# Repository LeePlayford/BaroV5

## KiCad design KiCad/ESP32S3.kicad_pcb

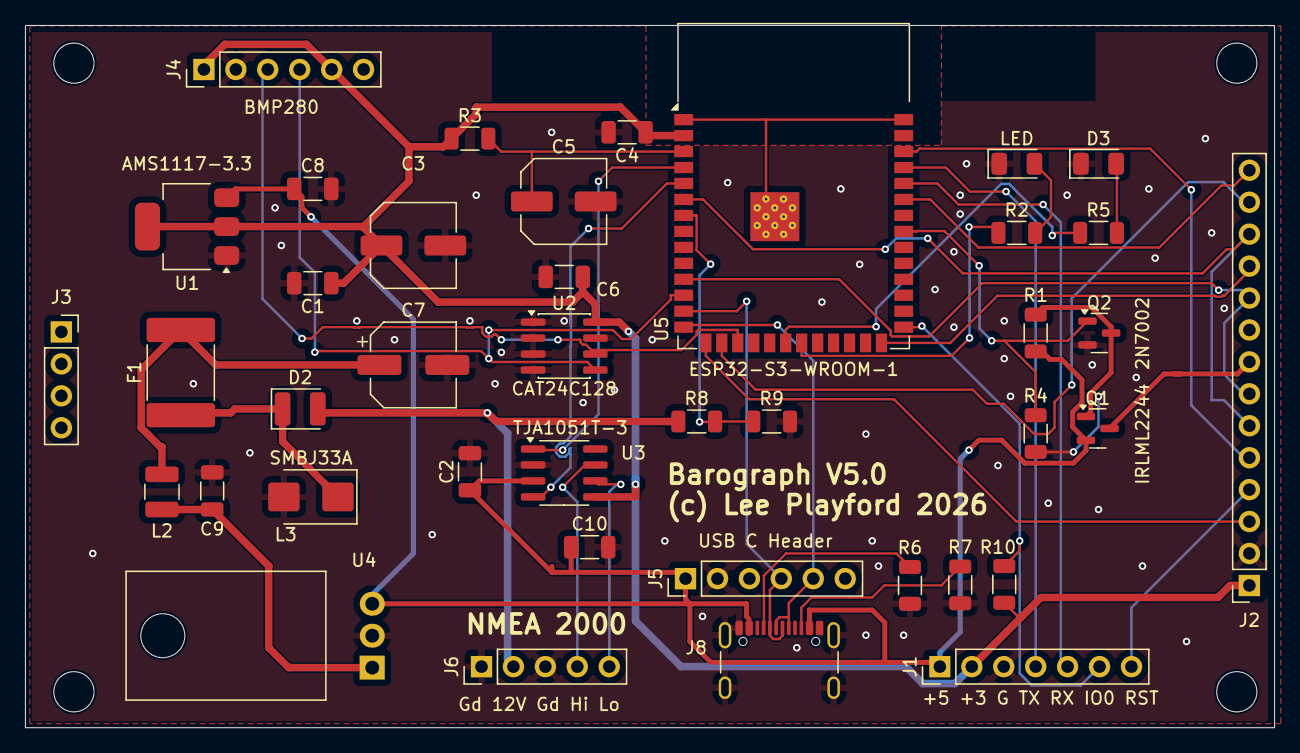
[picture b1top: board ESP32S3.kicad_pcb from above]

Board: 2 copper layers, 99.4 x 55.9 mm, 44 parts (0 on the bottom side), 38 nets.

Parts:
C1, C2, C4, C6, C8, C9, C10: 100nF; C_1206_3216Metric
C3: 22uF; C_Elec_6.3x5.4
C5: 10uF; C_Elec_6.3x5.4
C7: 100uf; CP_Elec_6.3x5.8
D1, D3: LED; LED_1206_3216Metric
D2: D; D_1210_3225Metric
F1: 2920L110/60MR; Fuse_2920_7451Metric
H1, H2, H3, H4: MountingHole; MountingHole_3.2mm_M3
J1: +5 +3 G TX RX IO0 RST; PinHeader_1x07_P2.54mm_Vertical
J2: Conn_01x14_Socket; PinSocket_1x14_P2.54mm_Vertical
J3: Conn_01x04_Socket; PinSocket_1x04_P2.54mm_Vertical
J4: BMP280; PinHeader_1x06_P2.54mm_Vertical
J5: USB C Header; PinHeader_1x06_P2.54mm_Vertical
J6: Gd 12V Gd Hi Lo; PinHeader_1x05_P2.54mm_Vertical
J8: USB_C_Receptacle_USB2.0_16P; USB_C_Receptacle_GCT_USB4105-xx-A_16P_TopMnt_Horizontal
L2: 33uH; L_1210_3225Metric
L3: SMBJ33A; D_SMB
Q1: IRLML2244; SOT-23
Q2: 2N7002; SOT-23
R1: 1k; R_1206_3216Metric
R2, R5: 120R; R_1206_3216Metric
R3, R4, R9, R10: 10K; R_1206_3216Metric
R6, R7: 5k1; R_1206_3216Metric
R8: 50k; R_1206_3216Metric
U1: AMS1117-3.3; SOT-223-3_TabPin2
U2: CAT24C128; SOIC-8_3.9x4.9mm_P1.27mm
U3: TJA1051T-3; SOIC-8_3.9x4.9mm_P1.27mm
U4: LM7805_TO220; TO-220-3_Horizontal_TabDown
U5: ESP32-S3-WROOM-1

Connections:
+3V3: C1.1, C3.1, C4.1, C6.1, J1.2, J2.1, J4.1, J4.5, R3.1, R10.1, U1.2 (VO), U2.8 (VCC), U3.5 (VIO), U5.2 (3V3)
+5V: C2.1, C8.1, C10.1, J1.1, J5.1, J8.A4 (VBUS), J8.A9 (VBUS), J8.B4 (VBUS), J8.B9 (VBUS), Q1.2 (S), R1.2, U1.3 (VI), U3.3 (VCC), U4.3 (VO)
+12V: D2.2 (A), J6.2, R8.1
BACKLIGHT: J2.8, Q1.3 (D)
BL_GPIO: Q2.1 (G), R4.1, U5.33 (IO40)
CAN_H: J6.4, U3.7 (CANH)
CAN_L: J6.5, U3.6 (CANL)
CAN_RX: U3.4 (RXD), U5.5 (IO5)
CAN_TX: U3.1 (TXD), U5.4 (IO4)
EN_RESET: J1.7, J2.4
GND: C1.2, C2.2, C3.2, C4.2, C5.2, C6.2, C7.2, C8.2, C9.2, C10.2, D1.1 (K), D3.1 (K), J1.3, J2.2, J4.2, J5.2, J6.1, J6.3, J8.A1 (GND), J8.A12 (GND), J8.B1 (GND), J8.B12 (GND), J8.S1 (SHIELD), L3.2, Q2.2 (S), R4.2, R6.2, R7.2, R9.2, U1.1 (GND), U2.1 (A0), U2.2 (A1), U2.3 (A2), U2.4 (GND), U2.7 (WP), U3.2 (GND), U4.2 (GND)
IO0: J1.6, R10.2, U5.27 (IO0)
LCD_CLK: J2.7, J2.10, U5.11 (IO18)
LCD_CS: J2.3, U5.15 (IO3)
LCD_MOSI: J2.6, J2.12, U5.6 (IO6)
LCD_RS: J2.5, U5.38 (IO2)
LED_01: R5.1, U5.20 (IO12)
LED_02: R2.1, U5.21 (IO13)
unnamed: C7.1, F1.2, L2.1
unnamed: D1.2 (A), R2.2
unnamed: D2.1 (K), F1.1, L3.1
unnamed: D3.2 (A), R5.2
unnamed: J8.A5 (CC1), R6.1
unnamed: J8.B5 (CC2), R7.1
unnamed: Q1.1 (G), Q2.3 (D), R1.1
unnamed: C9.1, L2.2, U4.1 (VI)
unnamed: C5.1, R3.2, U5.3 (EN)
unnamed: U5.1 (GND), U5.40 (GND), U5.41 (GND)
SCL: J4.3, U2.6 (SCL), U5.17 (IO9)
SDA: J4.4, U2.5 (SDA), U5.12 (IO8)
TP_CS: J2.11, U5.26 (IO45)
TP_INT: J2.14, U5.35 (IO42)
TP_MISO: J2.13, U5.16 (IO46)
USB_DN: J5.4, J8.A7 (D-), J8.B7 (D-), U5.13 (USB_D-)
USB_DP: J5.5, J8.A6 (D+), J8.B6 (D+), U5.14 (USB_D+)
U_RX: J1.5, U5.36 (RXD0)
U_TX: J1.4, U5.37 (TXD0)
VOLT_SENSE: R8.2, R9.1, U5.7 (IO7)

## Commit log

2026-02-21 Start Baro V5 repo
2026-04-05 V5 Source
